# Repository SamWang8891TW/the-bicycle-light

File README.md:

# the-bicycle-light
A project which provides users to make their easy-carry, easy-charge, and rich-function bicycle light.
中文使用者請點選上方的連結觀看中文版讀我檔案。

Current version: v0.1.0 (unfinished)
目前版本：v0.1.0 （尚未完成）

Introduction:
This is a bicycle light designed for easy install and remove from most of the bikes. With

PART I, I AM THE USER OF THE PRODUCT AND WANT TO UNDERSTAND HOW TO OPERATE:

1.Main Parts(detailed components press HERE):
    -Front light
        Installed on the front of the bicycle, equipped with a main light.
    -Rear light
        Installed on the rear of the bicycle, equipped with a main light and a pair of signal light.
    -Main control
        Installed on the handle of the bicycle, being as the control(remote) of the whole system.

2.Functionalities(
Note the manual is avilable as a pdf file in the repo(will be uploaded).):

  Front light: 
    -It has a white light strip which can light up the road infront of you. It has a button and a indicate led light. 
    -The button is used as single-operation mode which user decided to use it without a main control connected. When the button is pressed, the light can be switched on or off without the main control.
    -The led is a multi-funtional indicate light. 
        LED ON --> Light is on or the device is charging(when plugged). 
        LED OFF --> Light is off or fully charged(when plugged).
        LED FLAHING --> Battery low.
       
  Rear light:
    -It has three light strip, main read light(red) and left/right light(yellow) for turing singals. It has a button and a indicate led light. 
    -The button is used as single-operation mode which user decided to use it without a main control connected. When the button is pressed, it then disable all ongoing turing signal light and proceed being a switch of the main light. Turning singla light is not accessable while is single-operation mode.
    -The led is a multi-funtional indicate light. 
        LED ON --> Main light is on or the device is charging(when plugged). 
        LED OFF --> Main light is off or fully charged(when plugged).
        LED FLAHING --> Battery low.
   
  Main control:
    -User can control the whole system using is control.
    -It has 4 buttons: Main lights switch, left turning signal, right turning signal and dual flash(warning light).
    -It has 5 LEDs, indicating: Head(Front) light on/off, rear light on/off, left turning signal on/off and right turning signal on/off.
    -When the button is pressed, the vibrator vibrates(and the buzzor beeps if the user has enabled via the code), it then turn the light on or off depend on which button user pressed. To confirm the operation, user can view the indicate LEDs to make sure that they did the operation correctly. Note that the indicate LED does not flash as the real light, constantly on instead.

3.Instructions
    (1). To use the light, first user take out the lights and the main control from the charging case. Please check the battery level by watching the indicating LED is flasing or not.
    (2). To installed the front and rear light, user needs to untie the hook and loop tape, then tie the lights on the prefered place of the bicycle.
    (3). (OPTIONAL) To install the main control, user needs to untie the hook and loop take of the control and do the same thing as the light. Please make sure that user is accessable with their hand during riding the biycle.
    (4). User needs to test every function of the light before the ride, if any issues please create an ISSUE.
    (5). After the ride user then took off the lights and controler and put then back into the charging case. Please wait and see the charging light lids up before closing the case.

Please kindly check the pcb version before doing any operation.
Files:

-pcb:
    Contained the every version of the pcb. Please notice:
      1.Version 0.0.1 has the BJT be as the switch, but failed. So the pin C and E is shorted via soldering.
      2.Resistor and other components naming and ordering may not be as same across multiple versions.

-program:
    Contained the Arduino programm of the device. Currently the programm is suitale for all versions of the PCB.
    
-case:
    Contained f3d and stl files of the case for the lights. This is not necessary since you can designed your own version of it. *f3d is for Fusion360 use only!

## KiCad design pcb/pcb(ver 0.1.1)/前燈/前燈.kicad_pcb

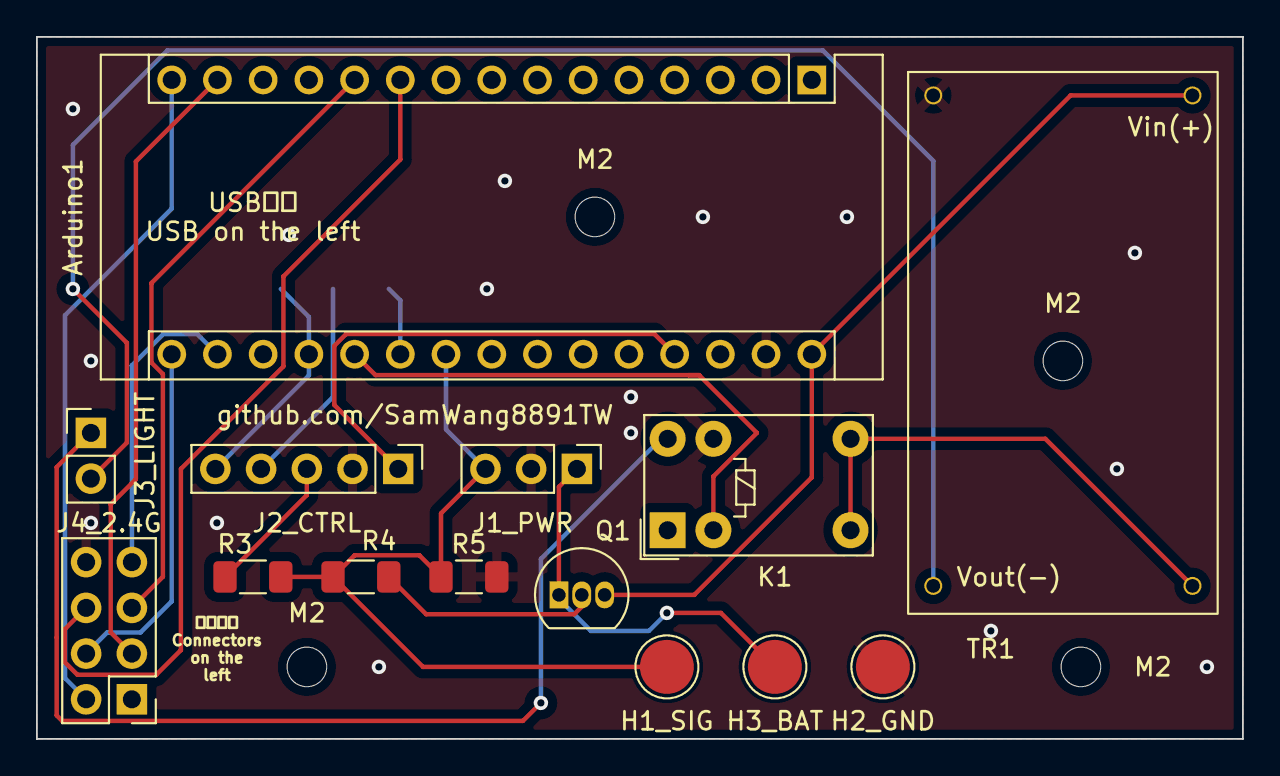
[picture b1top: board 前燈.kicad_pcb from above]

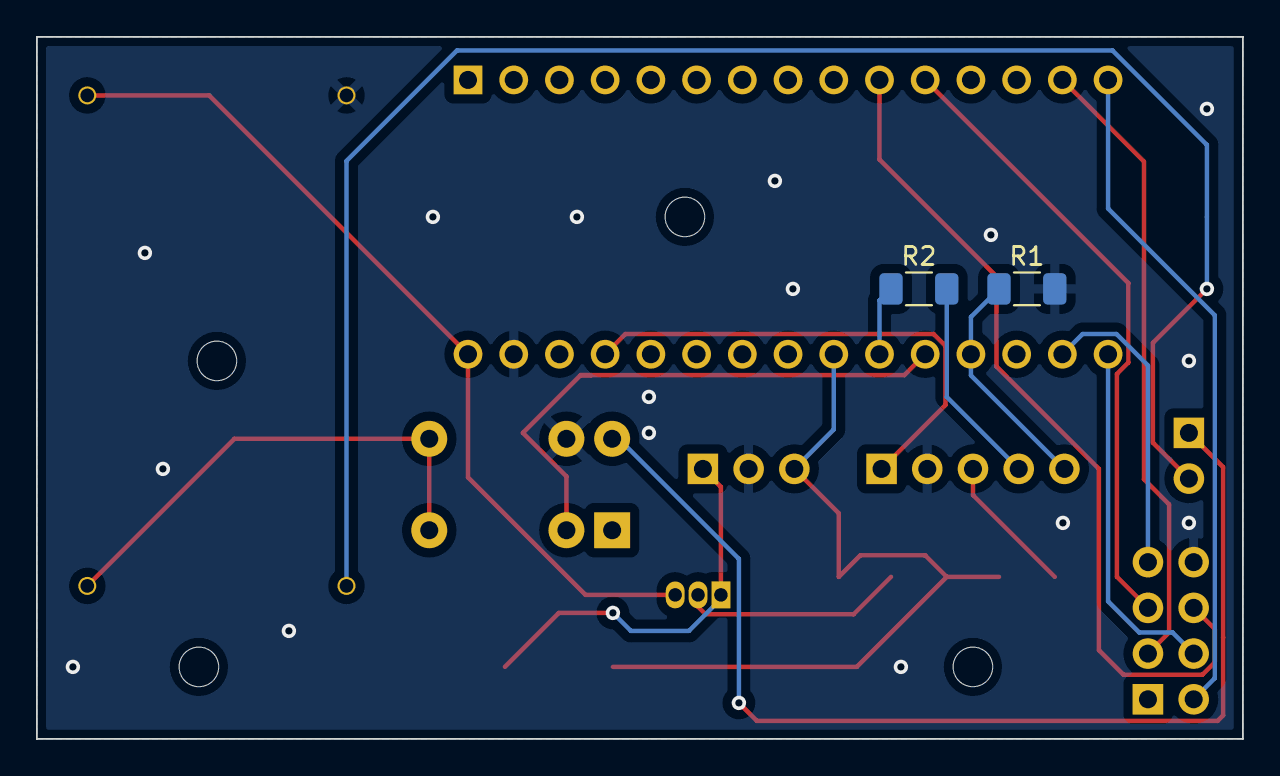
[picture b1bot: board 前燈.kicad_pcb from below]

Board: 2 copper layers, 67.0 x 39.0 mm, 20 parts (2 on the bottom side), 20 nets.

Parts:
Arduino1: Arduino_Nano
H1_SIG: SIG; TestPoint_Pad_D3.0mm
H2_GND: GND; TestPoint_Pad_D3.0mm
H3_BAT: BAT; TestPoint_Pad_D3.0mm
J1_PWR: PowerCONN; PinHeader_1x03_P2.54mm_Vertical
J2_CTRL: CtrlCONN; PinHeader_1x05_P2.54mm_Vertical
J3_LIGHT: LightCONN; PinHeader_1x02_P2.54mm_Vertical
J4_2.4G: 2.4G_CONN; PinHeader_2x04_P2.54mm_Vertical
K1: G5V-1; Relay_SPDT_Omron_G5V-1
M2, M2#2, M2#3, M2#4: MountingHole_2.2mm_M2
Q1: 2N4355; TO-92_Inline
R1, R2, R3: 330Ω; R_1206_3216Metric_Pad1.30x1.75mm_HandSolder
R4: 100kΩ; R_1206_3216Metric_Pad1.30x1.75mm_HandSolder
R5: 20kΩ; R_1206_3216Metric_Pad1.30x1.75mm_HandSolder
TR1: Micro3608_1166A_MicroUSB_Module

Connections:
Earth: Arduino1.29 (GND), H2_GND.1, J1_PWR.2 (Ground), J2_CTRL.2, J4_2.4G.8 (GND), K1.9, R1.2, R5.2, TR1.1 (Vin(-))
unnamed: Arduino1.10 (D7), J4_2.4G.6 (CE)
unnamed: Arduino1.11 (D8), J4_2.4G.5 (CSN)
unnamed: Arduino1.14 (D11(MOSI)), J4_2.4G.3 (MOSI)
unnamed: Arduino1.15 (D12(MISO)), J4_2.4G.2 (MISO)
unnamed: Arduino1.16 (D13), J4_2.4G.4 (SCLK)
unnamed: Arduino1.17 (3V3), J4_2.4G.7 (VCC)
unnamed: Arduino1.19 (A0), J2_CTRL.5, R1.1
unnamed: Arduino1.20 (A1), K1.2
unnamed: Arduino1.21 (A2), R2.1
unnamed: Arduino1.27 (5V), J2_CTRL.1
unnamed: H3_BAT.1, J1_PWR.1 (Power), Q1.1 (E)
unnamed: J2_CTRL.3, R3.1
unnamed: J2_CTRL.4, R2.2
unnamed: J3_LIGHT.1, K1.10
unnamed: J3_LIGHT.2, TR1.3 (Out(-))
unnamed: K1.5, K1.6, TR1.4 (Out(+))
unnamed: Q1.2 (B), R4.1
SIG: Arduino1.22 (A3), H1_SIG.1, J1_PWR.3 (Charging_Signal), R3.2, R4.2, R5.1
VIN: Arduino1.30 (VIN), Q1.3 (C), TR1.2 (Vin(+))

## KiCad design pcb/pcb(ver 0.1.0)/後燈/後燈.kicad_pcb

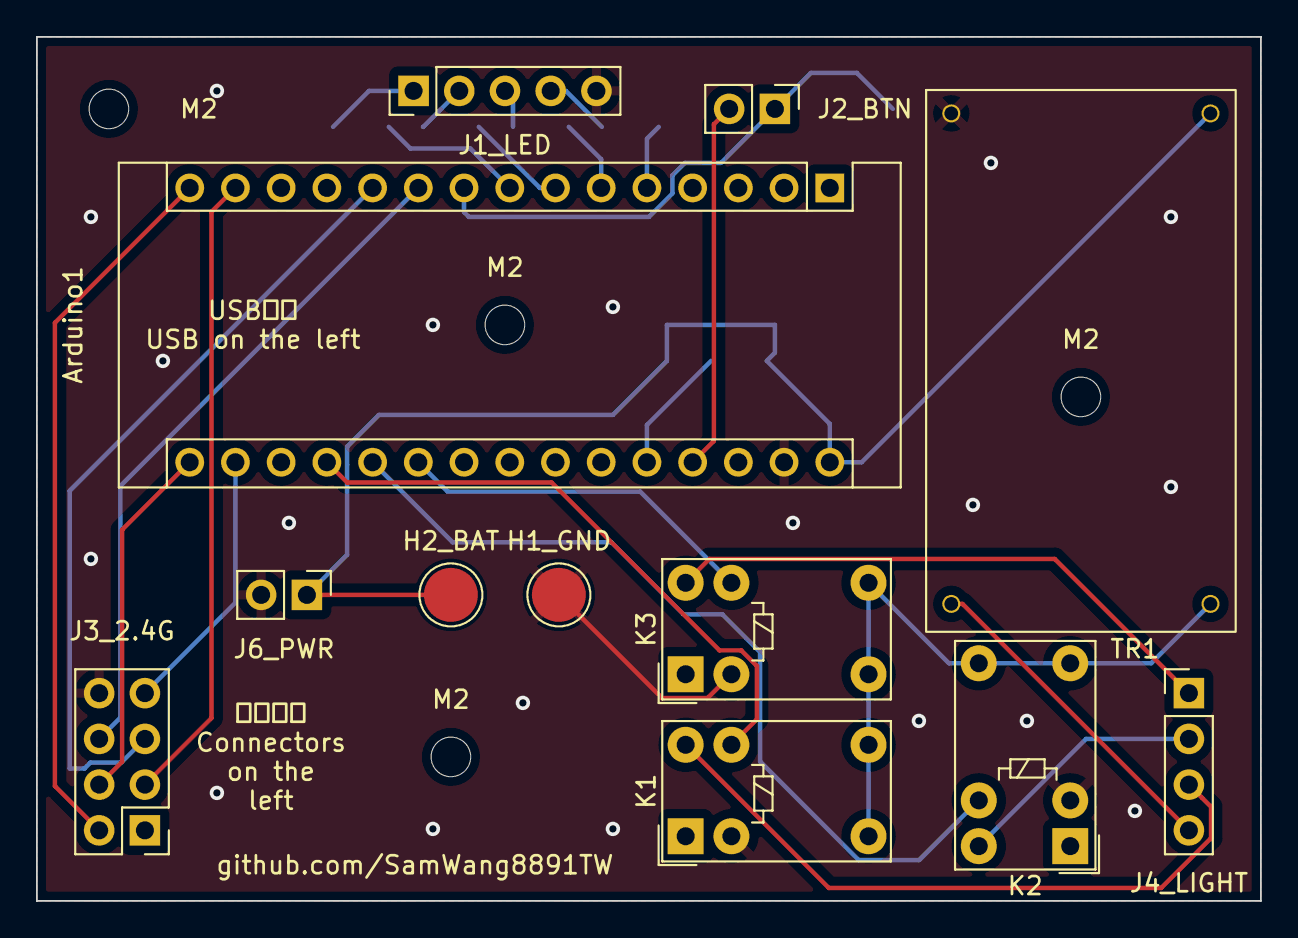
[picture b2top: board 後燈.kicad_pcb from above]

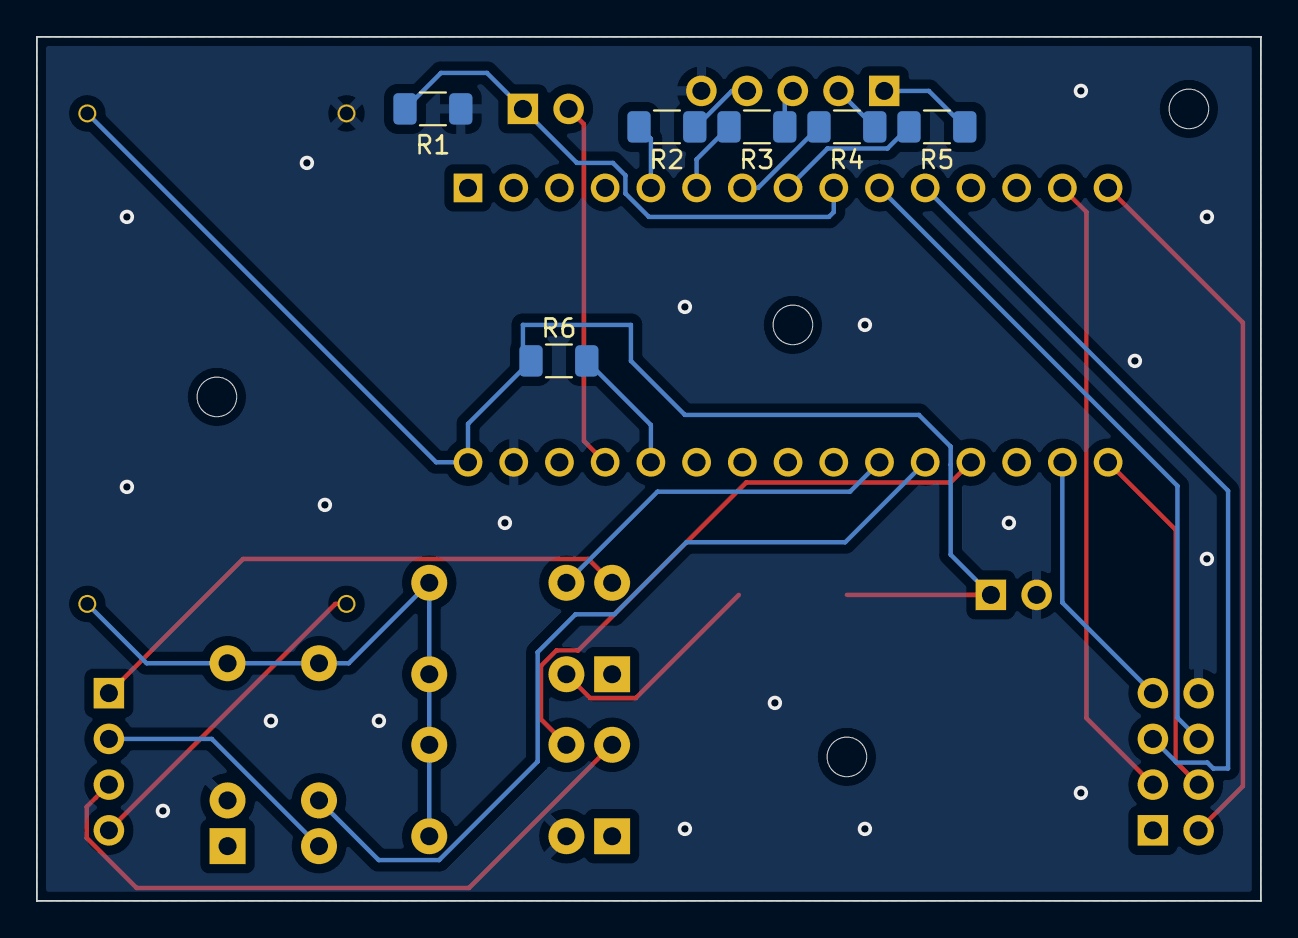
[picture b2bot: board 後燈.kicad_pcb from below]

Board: 2 copper layers, 68.0 x 48.0 mm, 22 parts (6 on the bottom side), 27 nets.

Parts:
Arduino1: Arduino_Nano
H1_GND: GND; TestPoint_Pad_D3.0mm
H2_BAT: BAT; TestPoint_Pad_D3.0mm
J1_LED: LedCONN; PinHeader_1x05_P2.54mm_Vertical
J2_BTN: BtnCONN; PinHeader_1x02_P2.54mm_Vertical
J3_2.4G: 2.4G_CONN; PinHeader_2x04_P2.54mm_Vertical
J4_LIGHT: LightCONN; PinHeader_1x04_P2.54mm_Vertical
J6_PWR: PWRConn; PinHeader_1x02_P2.54mm_Vertical
K1, K2, K3: G5V-1; Relay_SPDT_Omron_G5V-1
M2, M2#2, M2#3, M2#4: MountingHole_2.2mm_M2
R1, R2, R3, R4, R5: 330Ω; R_1206_3216Metric_Pad1.30x1.75mm_HandSolder
R6: 500kΩ; R_1206_3216Metric_Pad1.30x1.75mm_HandSolder
TR1: Micro3608_1166A_MicroUSB_Module

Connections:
5V: Arduino1.27 (5V), J2_BTN.2
Earth: Arduino1.29 (GND), H1_GND.1, J1_LED.5, J3_2.4G.8 (GND), J6_PWR.2, K1.2, K2.2, K3.2, R1.2, TR1.1 (Vin(-))
unnamed: Arduino1.5 (D2), R2.2
unnamed: Arduino1.6 (D3), R3.2
unnamed: Arduino1.7 (D4), R4.2
unnamed: Arduino1.8 (D5), R5.2
unnamed: Arduino1.9 (D6), J2_BTN.1, R1.1
unnamed: Arduino1.10 (D7), J3_2.4G.6 (CE)
unnamed: Arduino1.11 (D8), J3_2.4G.5 (CSN)
unnamed: Arduino1.14 (D11(MOSI)), J3_2.4G.3 (MOSI)
unnamed: Arduino1.15 (D12(MISO)), J3_2.4G.2 (MISO)
unnamed: Arduino1.16 (D13), J3_2.4G.4 (SCLK)
unnamed: Arduino1.17 (3V3), J3_2.4G.7 (VCC)
unnamed: Arduino1.19 (A0), K1.9
unnamed: Arduino1.20 (A1), K2.9
unnamed: Arduino1.21 (A2), K3.9
unnamed: Arduino1.26 (A7), R6.2
unnamed: J1_LED.1, R5.1
unnamed: J1_LED.2, R4.1
unnamed: J1_LED.3, R3.1
unnamed: J1_LED.4, R2.1
unnamed: J4_LIGHT.1, K3.10
unnamed: J4_LIGHT.2, K2.10
unnamed: J4_LIGHT.3, K1.10
unnamed: J4_LIGHT.4, TR1.3 (Out(-))
unnamed: K1.5, K1.6, K2.5, K2.6, K3.5, K3.6, TR1.4 (Out(+))
VIN: Arduino1.30 (VIN), H2_BAT.1, J6_PWR.1, R6.1, TR1.2 (Vin(+))

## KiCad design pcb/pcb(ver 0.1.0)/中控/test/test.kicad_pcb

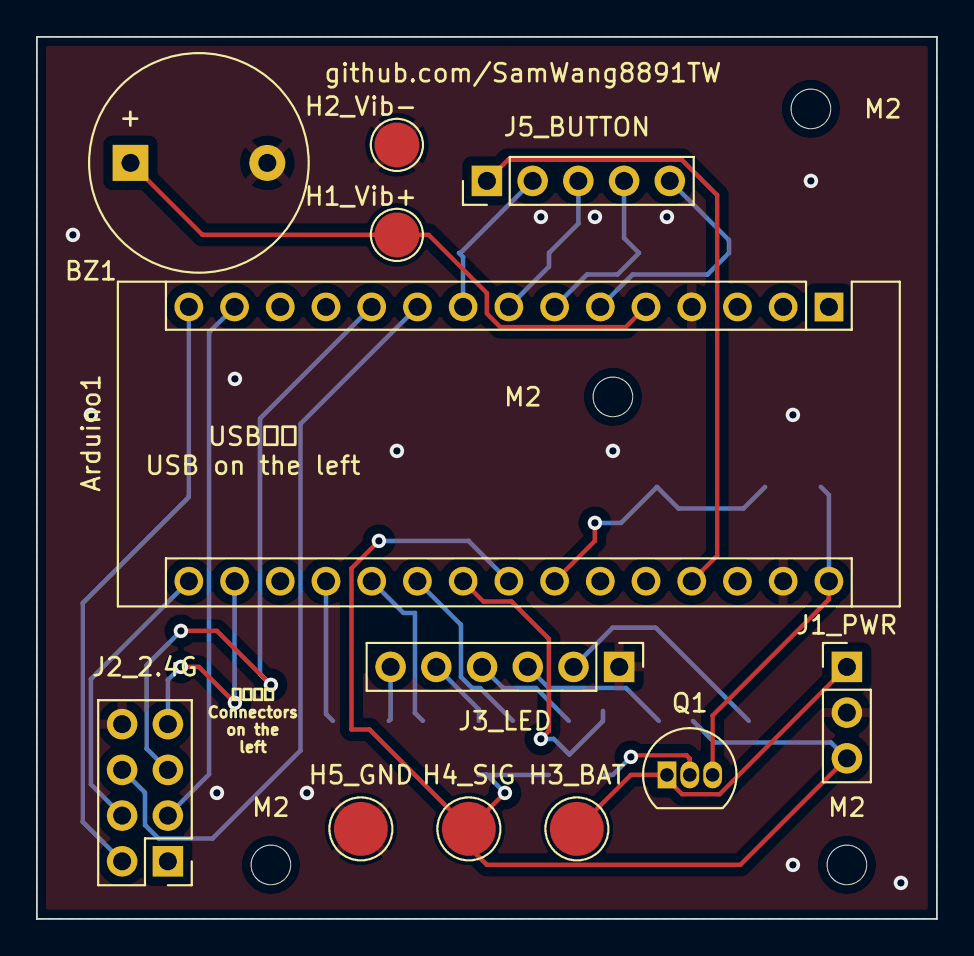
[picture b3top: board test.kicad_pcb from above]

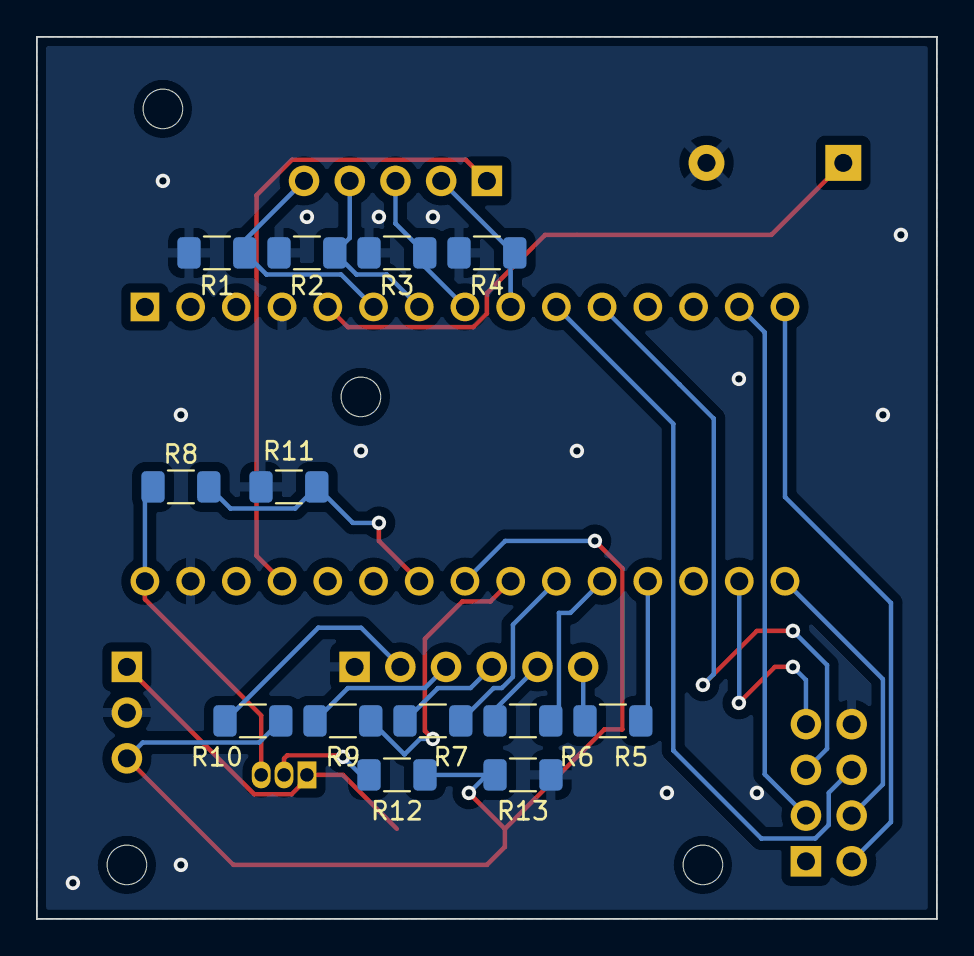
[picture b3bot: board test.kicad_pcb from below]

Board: 2 copper layers, 50.0 x 49.0 mm, 29 parts (13 on the bottom side), 27 nets.

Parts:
Arduino1: Arduino_Nano
BZ1: Buzzer; Buzzer_12x9.5RM7.6
H1_Vib+, H2_Vib-: Vibrator_Soder_Hole; TestPoint_Pad_D2.5mm
H3_BAT: BAT; TestPoint_Pad_D3.0mm
H4_SIG: SIG; TestPoint_Pad_D3.0mm
H5_GND: GND; TestPoint_Pad_D3.0mm
J1_PWR: PowerCONN; PinHeader_1x03_P2.54mm_Vertical
J2_2.4G: 2.4G_CONN; PinHeader_2x04_P2.54mm_Vertical
J3_LED: LED_CONN; PinHeader_1x06_P2.54mm_Vertical
J5_BUTTON: Button_CONN; PinHeader_1x05_P2.54mm_Vertical
M2, M2#2, M2#3, M2#4: MountingHole_2.2mm_M2
Q1: 2N4355; TO-92_Inline
R1, R2, R3, R4, R5, R6, R7, R9, R10: 330Ω; R_1206_3216Metric_Pad1.30x1.75mm_HandSolder
R8, R11: 500kΩ; R_1206_3216Metric_Pad1.30x1.75mm_HandSolder
R12: 100kΩ; R_1206_3216Metric_Pad1.30x1.75mm_HandSolder
R13: 20kΩ; R_1206_3216Metric_Pad1.30x1.75mm_HandSolder

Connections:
5V: Arduino1.27 (5V), J5_BUTTON.1
Earth: Arduino1.4 (GND), Arduino1.29 (GND), BZ1.2 (+), H2_Vib-.1, H5_GND.1, J1_PWR.2 (Ground), J2_2.4G.8 (GND), J3_LED.1, R1.2, R2.2, R3.2, R4.2, R11.2, R13.2
unnamed: Arduino1.5 (D2), BZ1.1 (-), H1_Vib+.1
unnamed: Arduino1.6 (D3), J5_BUTTON.5, R1.1
unnamed: Arduino1.7 (D4), J5_BUTTON.4, R2.1
unnamed: Arduino1.8 (D5), J5_BUTTON.3, R3.1
unnamed: Arduino1.9 (D6), J5_BUTTON.2, R4.1
unnamed: Arduino1.10 (D7), J2_2.4G.6 (CE)
unnamed: Arduino1.11 (D8), J2_2.4G.5 (CSN)
unnamed: Arduino1.14 (D11(MOSI)), J2_2.4G.3 (MOSI)
unnamed: Arduino1.15 (D12(MISO)), J2_2.4G.2 (MISO)
unnamed: Arduino1.16 (D13), J2_2.4G.4 (SCLK)
unnamed: Arduino1.17 (3V3), J2_2.4G.7 (VCC)
unnamed: Arduino1.19 (A0), R5.2
unnamed: Arduino1.20 (A1), R6.2
unnamed: Arduino1.21 (A2), R7.1
unnamed: Arduino1.22 (A3), R9.1
unnamed: Arduino1.24 (A5), R8.2, R11.1
unnamed: Arduino1.30 (VIN), Q1.3 (C), R8.1
unnamed: H3_BAT.1, J1_PWR.1 (Power), Q1.1 (E)
unnamed: J3_LED.2, R10.1
unnamed: J3_LED.3, R9.2
unnamed: J3_LED.4, R7.2
unnamed: J3_LED.5, R6.1
unnamed: J3_LED.6, R5.1
unnamed: Q1.2 (B), R12.1
SIG: Arduino1.23 (A4), H4_SIG.1, J1_PWR.3 (Charging_Signal), R10.2, R12.2, R13.1

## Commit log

2022-07-06 Update LICENSE
2022-07-06 Add files via upload
    v0.1 alpha
2022-12-07 Progress upload
2022-12-26 New!
2023-01-02 New!
    delay() removed.
2023-04-12 new thing?
2023-05-03 New update!
